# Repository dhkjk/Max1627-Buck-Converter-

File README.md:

# Max1627-Buck-Converter-
By: Dae Kim
Final project for EE348
PCB layout for a MAX1627 chip as a buck converter

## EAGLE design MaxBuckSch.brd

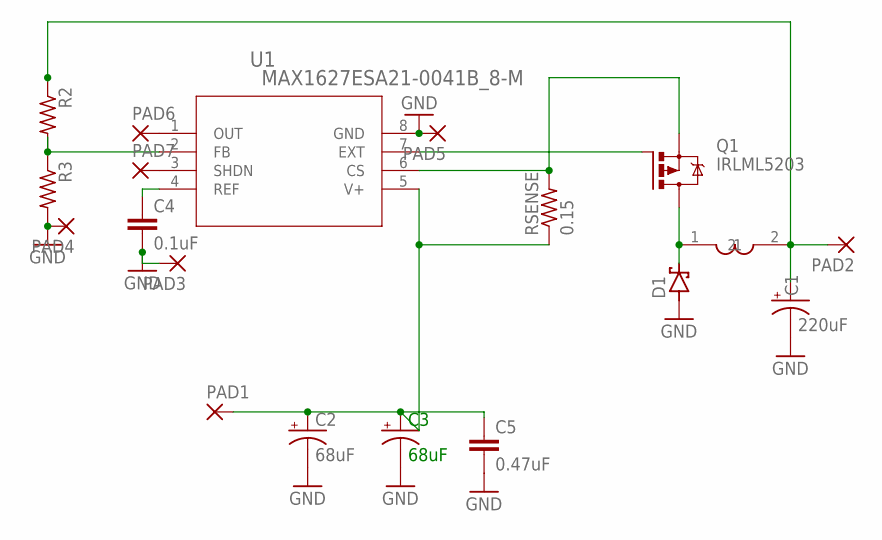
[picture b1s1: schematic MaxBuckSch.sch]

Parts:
C1: 220uF; D/7343-31W
C2, C3: 68uF; D/7343-31W
C4: 0.1uF; C0805K
C5: 0.47uF; C0805K
D1: SCHOTTKY-DIODESMC; SMC
PAD1, PAD2, PAD3, PAD4, PAD5, PAD6, PAD7: 2,15/1,0
Q1: IRLML5203; MICRO3
R2, R3: R-US_R0805W; R0805W
RSENSE: 0.15; R0805W
U1: MAX1627ESA21-0041B_8-M; 21-0041B_8-M
U$1: EE348; INDUCTOR

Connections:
GND: C1.-, C2.-, C3.-, C4.2, C5.2, D1.A, PAD3.1, PAD4.1, PAD5.1, R3.2, U1.8 (GND)
unnamed: R2.2, R3.1, U1.2 (FB)
unnamed: C2.+, C3.+, C5.1, PAD1.1, RSENSE.1, U1.5 (V+)
unnamed: Q1.2 (S), RSENSE.2, U1.6 (CS)
unnamed: Q1.1 (G), U1.7 (EXT)
unnamed: C1.+, PAD2.1, R2.1, U$1.2
unnamed: D1.C, Q1.3 (D), U$1.1
unnamed: C4.1, U1.4 (REF)
unnamed: PAD6.1, U1.1 (OUT)
unnamed: PAD7.1, U1.3 (SHDN)

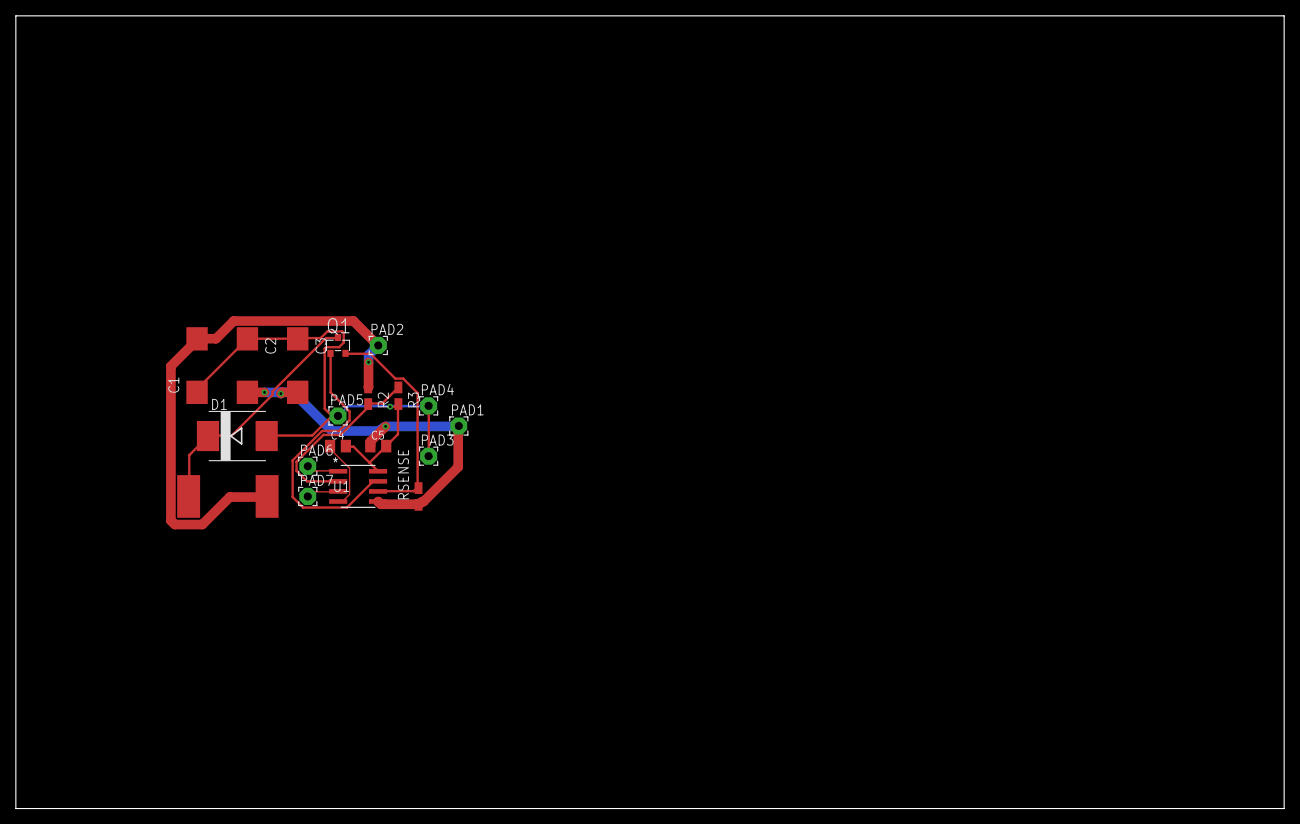
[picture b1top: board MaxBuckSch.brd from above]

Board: 2 copper layers, 160.0 x 100.0 mm, 19 parts (0 on the bottom side), 10 nets.
